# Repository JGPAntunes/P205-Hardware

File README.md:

# P205-Hardware
This repository was imported from GITLAB manualy, so no commits or branches are available.

This project aims to reliably obtain an ECG and all the signal metrics, and provide real-time alerts. 

These alerts would be sent to the medical staff, and through a graphical interface can confirm the patient ID, contact details and their location (GPS and/or cell triangulation). 

This does not change the fact that it is still a recording device, since the signals are recorded internally on an SD card 
This makes it possible for the data to be interpreted on a hospital environment, by the medical team.

PCB was designed from scratch for this usecase, the Signal Aquisition Medical Board (SAMB).

PCB Specifications:

	• Dual nRF52832 (one for data aquisition and one communications and overhaul system)

	• External RAM for MCU communication bridge

	• ADS1298 and ADS1296 for data aquisition

	• Precision NTC temperature sensing

	• SIM7080G for NB-IoT and GNSS 

	• SD card datalogging

	• BLE comunication (via the master nRF MCU)

	• USB battery charging (type C, no PD charging)

	• Wireless battery charging

	• DSUB-15 connector for eletrodes cable

	• 5mm jack for NTC sensor

	• ESD protection

	• Defibrillator discharge protection

	• OLED display (SPI)

	• Buzzer

	• Small external PCB with UI buttons

PCB Details:

	• Dimentions: 100mm x 95mm.

	• Soldermask: Black.

	• 4 layer IS400 18µm/35µm.

	• Tolerances:

	o OL-TT-TP-PP: 0.100mm (camadas exteriores)

	o OL‐TW: 0.125mm

	o OAR: 0.100mm

	o Via size 0.1mm drill

	o BGA pitch 0.8mm

	• Ni/Au.

	• Double side PCBA.

	• 4 M3 PTH.

	• Star-ground

	• 3 seperated ground planes (analog, digital e power).

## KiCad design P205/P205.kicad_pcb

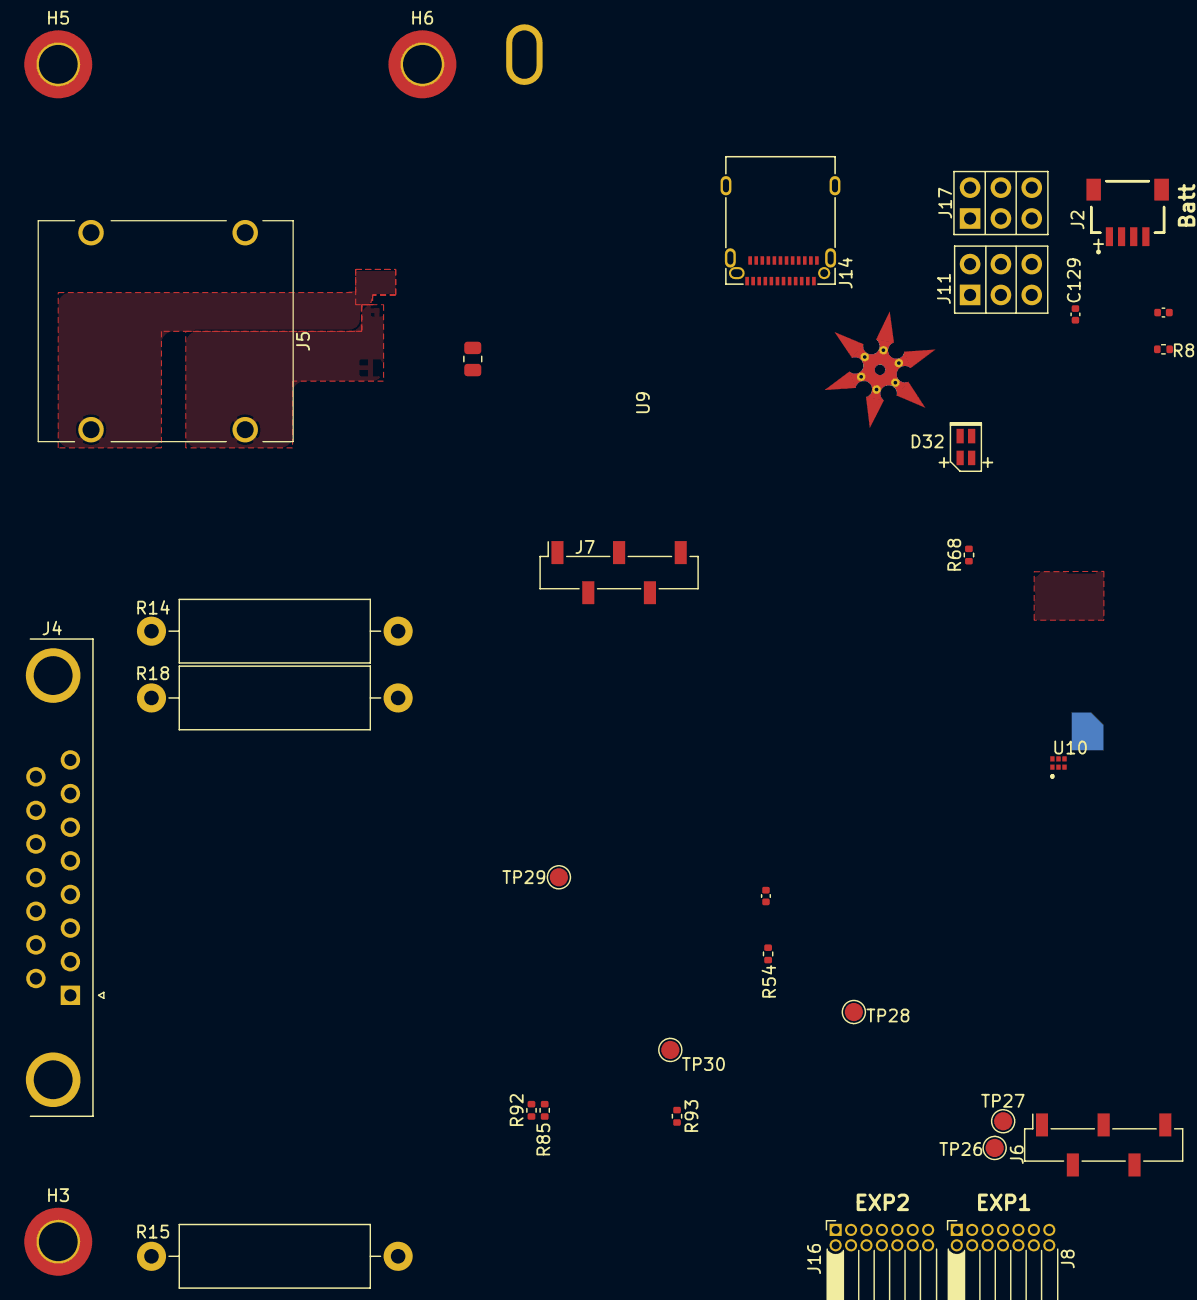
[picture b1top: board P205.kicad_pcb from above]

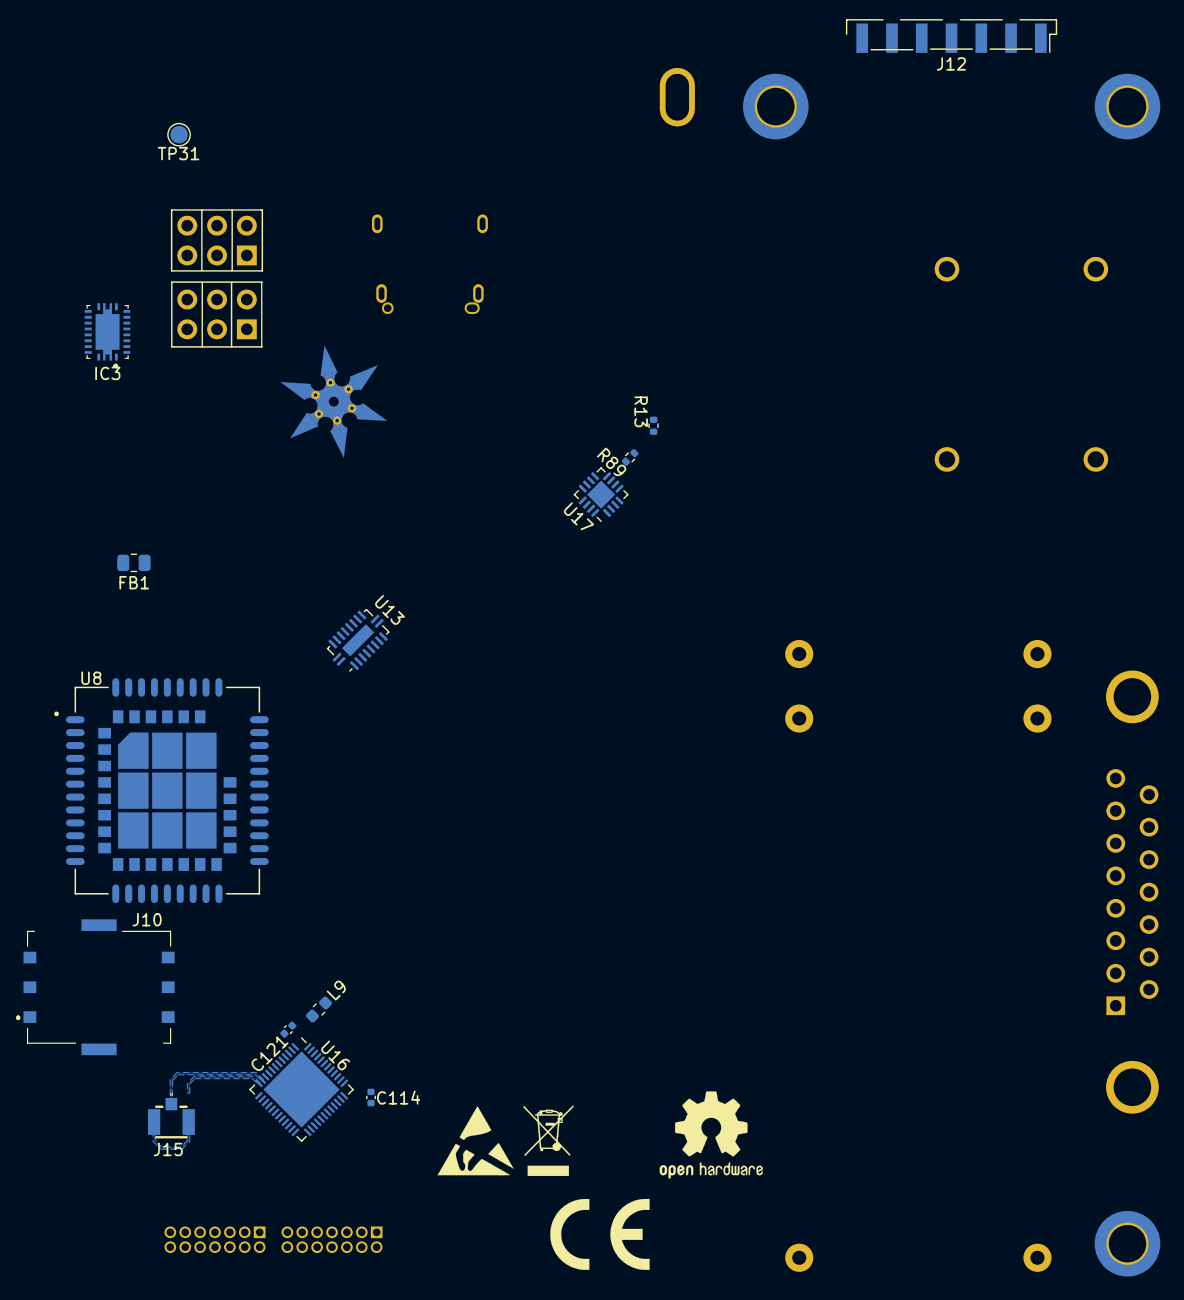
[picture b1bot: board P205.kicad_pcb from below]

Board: 4 copper layers, 50 parts (15 on the bottom side), 46 nets, no tracks yet.

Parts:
C61, C114: 12p; C_0402_1005Metric
C102, C129: 1u; C_0402_1005Metric
C121: 100n; C_0402_1005Metric
D32: APHBM2012LVBDZGKC; LED_2C
FB1, FB2: BLM21SP601SH1D; R_0805_2012Metric
H3: MH3; MountingHole_3.2mm_M3_DIN965_Pad_TopBottom
H5, H6: MH4; MountingHole_3.2mm_M3_DIN965_Pad_TopBottom
IC3: BQ51050BRHLR
J2: Batt; M404010446
J4: ECG Connector; DSUB-15_Female_Horizontal_P2.77x2.84mm_EdgePinOffset7.70mm_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
J5: AudioJack2_Dual_Switch; NMJ4HHD2
J6, J7: PROG; PinSocket_1x05_P2.54mm_Vertical_SMD_Pin1Right
J8: EXP1; PinSocket_2x07_P1.27mm_Horizontal
J10: SIM_Card; SIM8051601401A
J11, J17: USB/BATT; PinHeader_2x03_P2.54mm_Vertical
J12: Button; ConnButton
J14: 12401598E4#2A; AMPHENOL_12401598E4#2A
J15: U.FL-R-SMT-1(10); CONUFL001-SMD
J16: EXP2; PinSocket_2x07_P1.27mm_Horizontal
L9: 10u; L_0603_1608Metric
NT1: STARGROUND; NINJA_STAR_GROUND_CUT
R13, R93: 5.1k; R_0402_1005Metric
R14, R15, R18: 100k; R_Axial_DIN0516_L15.5mm_D5.0mm_P20.32mm_Horizontal
R54: 0; R_0402_1005Metric
R68: 330; R_0402_1005Metric
R80: 10k; R_0402_1005Metric
R85, R92: 71.5k; R_0402_1005Metric
R89: NC; R_0402_1005Metric
TP26: MOSI; TestPoint_Pad_D1.5mm
TP27: CLK; TestPoint_Pad_D1.5mm
TP28: MISO; TestPoint_Pad_D1.5mm
TP29, TP30: VCAP1; TestPoint_Pad_D1.5mm
TP31: KEYCHAIN; TestPoint_Pad_D1.5mm
U8: SIM7080G; XCVR_SIM7080G
U9: OLED_2.49; PinHeader_1x07_P2.54mm_Vertical_SMD_Pin1Right
U10: LNA; BGU7007115
U13: NXB0108; WQFN-20-1EP_2.5x4.5mm_P0.5mm_EP1x2.9mm
U16: nRF52832; QFN-48-1EP_6x6mm_P0.4mm_EP4.6x4.6mm
U17: PI5C3257; QFN-16-1EP_3x3mm_P0.5mm_EP1.7x1.7mm

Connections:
/AVCC: FB2.1, R54.1, R85.2, R92.2, R93.1
/BATT: FB1.1, J11.3, J11.4, J16.1, J16.2, J17.3, J17.4
/BATT_RAW: C102.1, IC3.4, J2.1, J11.5, J11.6, J17.5, J17.6
/DVCC: D32.1, J6.5, J7.5, J8.1, J8.2, J8.3, J8.5, J16.3, J16.4, J16.5, R89.1, U10.4, U13.19, U16.13, U16.36, U16.48, U17.16
/RST: J6.4, U16.24
/SIMCOM/SIMCARD_CLK: J10.3, U8.16
/SIMCOM/SIMCARD_DATA: J10.7, U8.15
/SIMCOM/SIMCARD_RST: J10.2, U8.17
/SIMCOM/SIMCARD_VDD: J10.1, U8.18
/SIMCOM/SIMCOM_CTS: U8.4, U13.5
/SIMCOM/SIMCOM_RTS: U8.3, U13.6
/SIMCOM/SIMCOM_RX: U8.1, U13.7
/SIMCOM/SIMCOM_TX: U8.2, U13.8
/SIMCOM/SIMCOM_VDD: FB1.2, U8.34, U8.35
/SIMCOM/VDD_EXT: U8.40, U13.2
/V1: J4.12, R14.2
/V2: J4.1, R15.2
/V5: J4.4, R18.2
/V_BUS: C129.1, D32.4, IC3.9, J11.1, J11.2, J14.A4, J14.A9, J14.B4, J14.B9, J17.1, J17.2
/uC1_AIN1_P0.03: J8.7, U16.5
/uC1_AIN2_P0.04: J8.10, U16.6
/uC1_AIN3_P0.05: J8.8, U16.7
/uC1_AIN4_P0.28: J16.8, U16.40
/uC1_AIN5_P0.29: J16.6, U16.41
/uC1_ECG_MISO: TP28.1, U16.16
/uC1_ECG_MOSI: TP26.1, U16.18
/uC1_ECG_SCLK: TP27.1, U16.17
/uC1_NRF52832/NFC1_ANT: J15.1, U16.11
/uC1_NRF52832/NFC2_ANT: J15.2, J15.3, U16.12
/uC1_NRF52832/SWDCLK: J6.3, U16.25
/uC1_NRF52832/SWDIO: J6.2, U16.26
/uC1_NRF52832/XC-: C114.2, U16.35
/uC1_P0.19: J8.4, U16.22
/uC1_P0.20: J8.6, U16.23
/uC1_P0.22: J16.9, U16.27
/uC1_P0.23: J16.7, U16.28
/uC2_uSD_CS: U17.1, U17.2
GNDD: C114.1, C121.2, J6.1, J7.1, J8.11, J8.12, J8.13, J8.14, J10.5, J16.10, J16.11, J16.12, J16.13, J16.14, NT1.2, U8.8, U8.13, U8.19, U8.21, U8.27, U8.30, U8.31, U8.33, U8.36, U8.37, U8.45, U8.63, U8.66, U8.67, U8.69, U8.70, U8.71, U8.72, U8.73, U8.74, U8.75, U8.76, U8.77, U10.1, U10.2, U13.1, U13.3, U13.4, U13.11, U13.17, U13.18, U13.20, U16.31, U16.45, U16.49, U17.3, U17.6, U17.8, U17.10, U17.13
GNDREF: C102.2, C129.2, IC3.1, IC3.11, IC3.20, IC3.21, J2.3, J2.4, J14.A1, J14.A12, J14.B1, J14.B12, J14.S1, NT1.3, R80.2
GNDS: J4.0, NT1.1
unnamed: C121.1, U16.1
unnamed: U8.39, U13.9
unnamed: R13.2, R89.2, U17.7
unnamed: J14.A6, J14.A7, J14.B6, J14.B7
unnamed: L9.2, U16.47
unnamed: R85.1, R92.1

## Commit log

2023-01-16 Images folder added
2023-01-16 Added schematic and a few images
